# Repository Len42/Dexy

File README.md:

# Dexy

_DX7-inspired FM synthesis with a Raspberry Pi Pico_

Dexy is a digital FM voice in a 10 HP module. Part of my [homebrew Eurorack synthesizer](https://lenp.net/synth/).

[See here](https://lenp.net/synth/dexy/) for more info.

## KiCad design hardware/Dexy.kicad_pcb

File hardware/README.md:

# Dexy Hardware

Dexy is a digital FM voice module based on an [RP2040 microcontroller](https://www.raspberrypi.com/documentation/microcontrollers/rp2040.html).

[See here](https://lenp.net/synth/dexy/hardware.html) for more info.

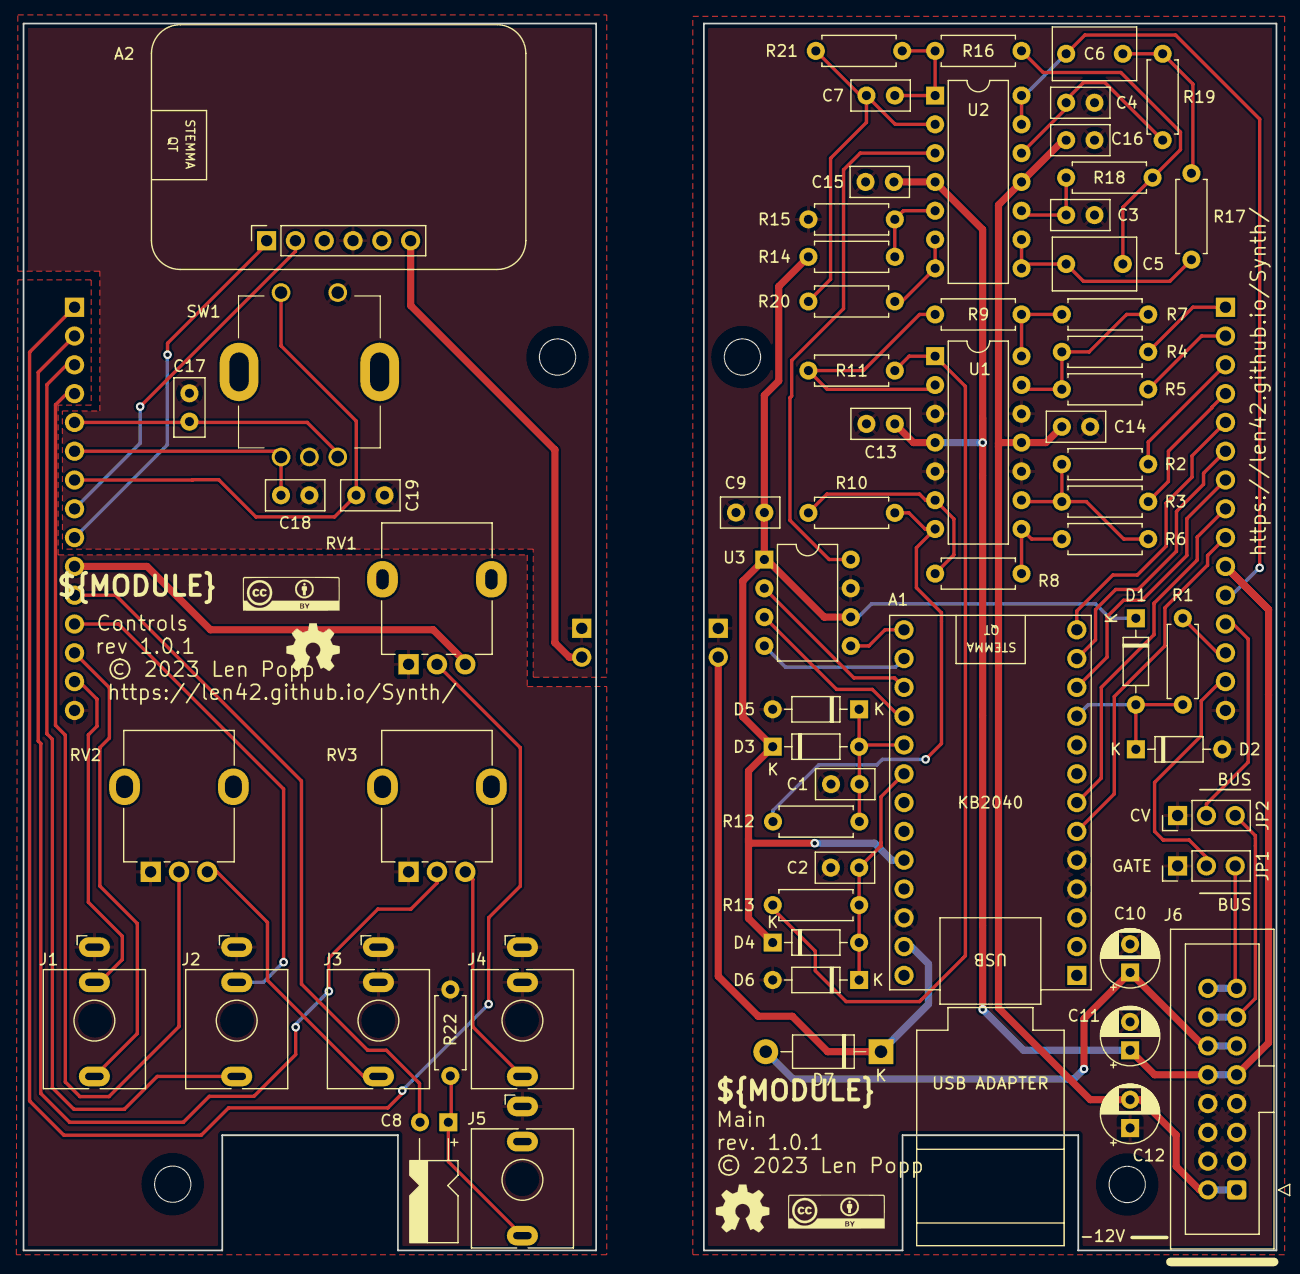
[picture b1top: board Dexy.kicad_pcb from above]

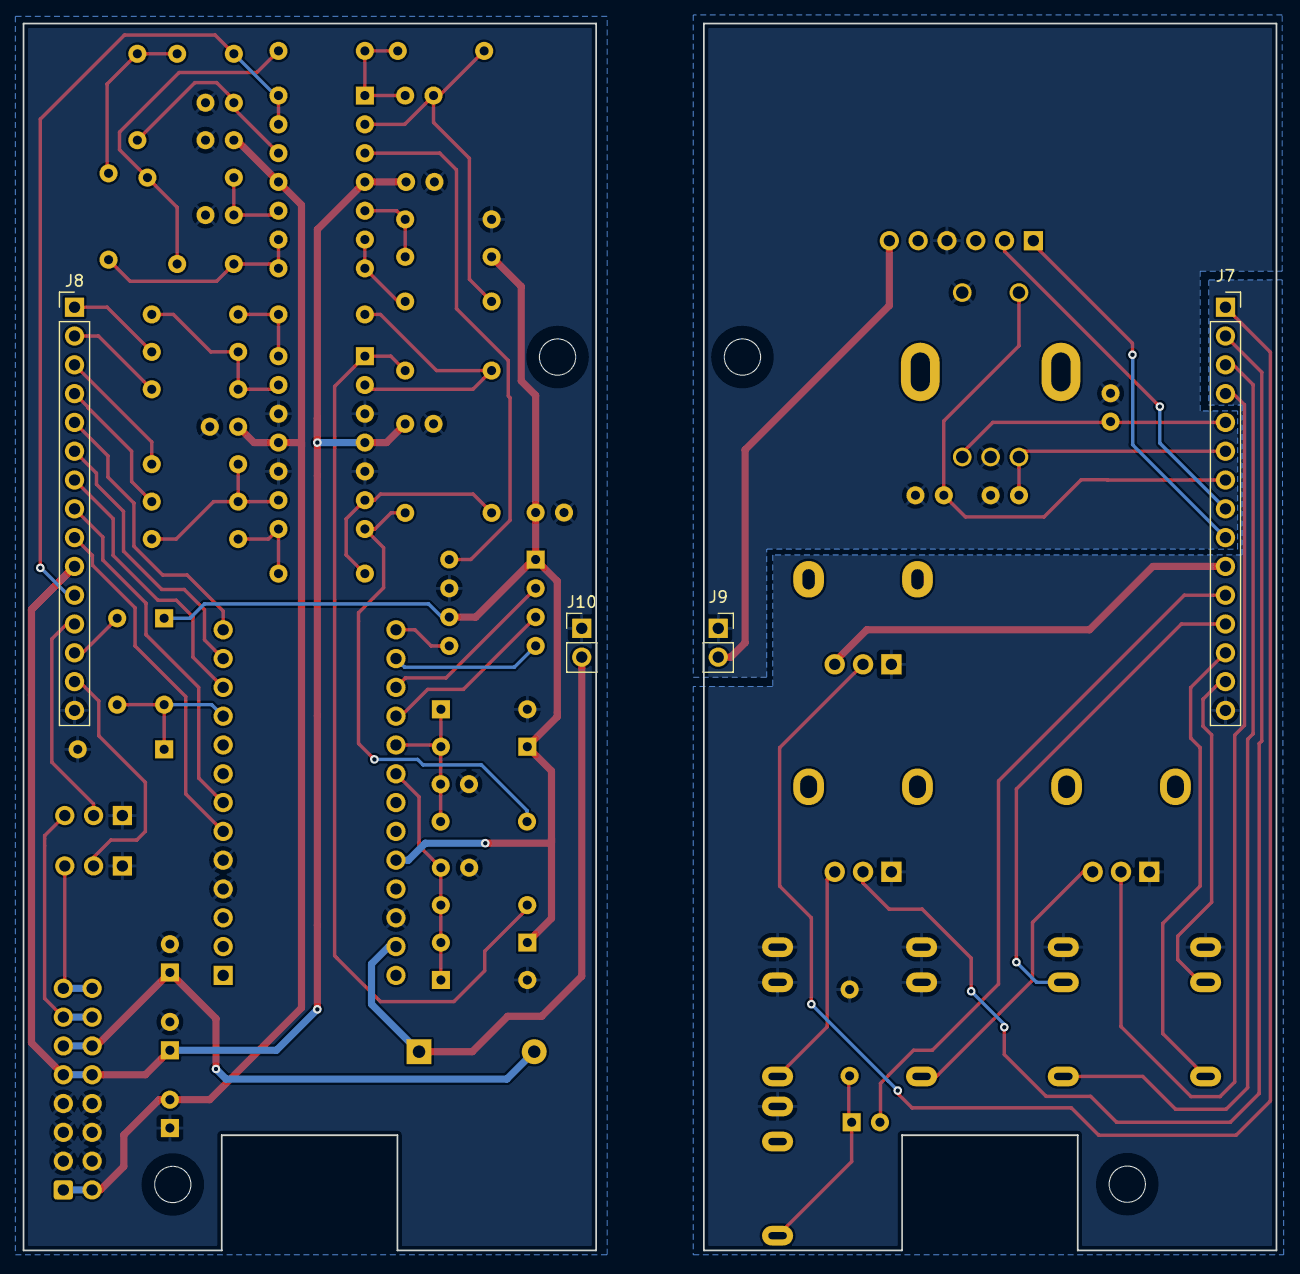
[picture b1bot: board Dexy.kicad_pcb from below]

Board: 2 copper layers, 110.5 x 108.2 mm, 78 parts (4 on the bottom side), 49 nets.

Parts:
A1: KB2040
A2: OLED_128x32; OLED_128x32_0.91in_NoHoles
A4: USB C Adapter 90deg; USB-C-Adapter-90-Outline
C1, C2, C3, C4: 150P; C_Disc_D5.0mm_W2.5mm_P2.50mm
C5, C6: 330P; C_Rect_L7.2mm_W4.5mm_P5.00mm
C7: 5P6; C_Disc_D5.0mm_W2.5mm_P2.50mm
C8: 2U2; CP_Radial_L7.0mm_D4.0mm_P2.50mm_Horiz
C9, C13, C14, C15, C16, C17, C18, C19: 100N; C_Disc_D5.0mm_W2.5mm_P2.50mm
C10, C11, C12: 10U; CP_Radial_D5.0mm_P2.50mm
D1, D2, D3, D4, D5, D6: 1N5711; D_DO-35_SOD27_P7.62mm_Horizontal
D7: 1N4001; D_DO-41_SOD81_P10.16mm_Horizontal
G1, G2: LOGO; Logo_CC_BY
G3, G4: LOGO; Logo_OSHW
H1, H2, H3, H4: MountingHole_M3; MountingHole_PCB_3.2mm_M3
J1, J2, J3, J4, J5: WQP-PJ398; Jack_3.5mm_QingPu_WQP-PJ398SM_Vertical
J6: Conn_Eurorack_16; IDC-Header-Eurorack-16-TH
J7: Controls_Left; PinSocket_1x15_P2.54mm_Vertical
J8: Main_Right; PinHeader_1x15_P2.54mm_Vertical
J9: Controls_Right; PinSocket_1x02_P2.54mm_Vertical
J10: Main_Left; PinHeader_1x02_P2.54mm_Vertical
JP1, JP2: Jumper_Pins_3_Bridged12; PinHeader_1x03_P2.54mm_Vertical
R1, R2, R6, R7, R8, R9, R12, R13: 100K; R_Axial_DIN0207_L6.3mm_D2.5mm_P7.62mm_Horizontal
R3: 499K; R_Axial_DIN0207_L6.3mm_D2.5mm_P7.62mm_Horizontal
R4: 120K; R_Axial_DIN0207_L6.3mm_D2.5mm_P7.62mm_Horizontal
R5: 82K; R_Axial_DIN0207_L6.3mm_D2.5mm_P7.62mm_Horizontal
R10, R11, R15: 33K; R_Axial_DIN0207_L6.3mm_D2.5mm_P7.62mm_Horizontal
R14, R20: 51K; R_Axial_DIN0207_L6.3mm_D2.5mm_P7.62mm_Horizontal
R16, R17, R18, R19: 47K; R_Axial_DIN0207_L6.3mm_D2.5mm_P7.62mm_Horizontal
R21: 200K; R_Axial_DIN0207_L6.3mm_D2.5mm_P7.62mm_Horizontal
R22: 1M; R_Axial_DIN0207_L6.3mm_D2.5mm_P7.62mm_Horizontal
RV1: 100K; Potentiometer_Alpha_RD901F-40-00D_Single_Vertical
RV2, RV3: 100K; Potentiometer_SongHuei_Single_Vertical
SW1: PEC11R-4x20x-S00xx; Encoder_Bourns_PEC11R_Switch
U1, U2: TL074; DIP-14_W7.62mm
U3: MCP4821; DIP-8_W7.62mm

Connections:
+3V3: A1.22 (3V3), C9.2, D1.1 (K), D3.1 (K), D4.1 (K), R14.1, U3.1 (V+), U3.6 (~SHDN)
+5V: A1.25 (V-RAW), A2.6 (VIN), D7.1 (K), J9.2, J10.2
+12V: C11.1, C13.1, C15.1, J6.9 (+12V), J6.10, J7.10, J8.10, RV1.3, U1.4 (V+), U2.4 (V+)
-12V: C12.2, C14.2, C16.2, J6.1 (-12V), J6.2, U1.11 (V-), U2.11 (V-)
/1V30: R20.1, U2.6 (-), U2.7
/10Vp-p: C7.2, R16.1, R21.2, U2.1
ADC-PITCH: A1.18 (A0(GPIO26/SCK1/CTS1/SDA1/PWM5A)), C1.1, D3.2 (A), D5.1 (K), R12.2
ADC-TIMBRE: A1.19 (A1(GPIO27/TX1/RTS1/SCL1/PWM5B)), C2.1, D4.2 (A), D6.1 (K), R13.2
AUDIO-OUT: C6.2, C8.2, J7.11, J8.11, U2.13 (-), U2.14
BUS-CV: J2.TN, J7.12, J8.12, JP2.2 (C)
BUS-GATE: J1.TN, J7.14, J8.14, JP1.2 (C)
DAC-OUT: U2.3 (+), U3.8 (Vout)
ENC-A: A1.12 (D8(GPIO8/RX1/TX1/SDA0/PWM4A)), C18.1, J7.6, J8.6, SW1.A
ENC-B: A1.13 (D9(GPIO9/CSN1/RX1/SCL0/PWM4B)), C17.1, J7.5, J8.5, SW1.B
ENC-SW: A1.11 (D7(GPIO7/TX0/RTS1/SCL1/PWM3B)), C19.1, J7.7, J8.7, SW1.S1
GATE: A1.10 (D6(GPIO6/SCK0/CTS1/SDA1/PWM3A)), D1.2 (A), D2.1 (K), R1.2
GND: A1.4 (GND), A1.5 (GND), A1.24 (GND), A2.4 (GND), C1.2, C2.2, C3.2, C4.2, C9.1, C10.2, C11.2, C12.1, C13.2, C14.1, C15.2, C16.1, C17.2, C18.2, C19.2, D2.2 (A), D5.2 (A), D6.2 (A), J1.S, J2.S, J3.S, J3.TN, J4.S, J4.TN, J5.S, J6.3 (GND), J6.4, J6.5 (GND), J6.6, J6.7 (GND), J6.8, J7.15, J8.15, J9.1, J10.1, JP1.1 (A), JP2.1 (A), R15.2, R22.2, RV1.1, RV2.1, RV3.1, SW1.C, SW1.S2, U1.3 (+), U1.5 (+), U1.10 (+), U1.12 (+), U3.7 (V-)
I2C-SCL: A1.7 (D3(GPIO3/TX0/RTS0/SCL1/PWM1B)), A2.2 (SCL), J7.8, J8.8
I2C-SDA: A1.6 (D2(GPIO2/SCK0/CTS0/SDA1/PWM1A)), A2.1 (SDA), J7.9, J8.9
IN-CV-PITCH: J2.T, J7.3, J8.3, R2.1
IN-CV-PITCH-MOD: J7.4, J8.4, R3.1, RV2.2
IN-CV-TIMBRE: J7.1, J8.1, R4.1, RV1.2
IN-CV-TIMBRE-MOD: J7.2, J8.2, R5.1, RV3.2
IN-GATE: J1.T, J7.13, J8.13, R1.1
unnamed: C5.1, R16.2, R18.1
unnamed: C6.1, R17.2, R19.1
unnamed: C8.1, J5.T, R22.1
unnamed: C10.1, D7.2 (A), J6.11 (+5V), J6.12
unnamed: J3.T, RV2.3
unnamed: J4.T, RV3.3
unnamed: J6.13 (CV), J6.14, JP2.3 (B)
unnamed: J6.15 (GATE), J6.16, JP1.3 (B)
unnamed: R6.2, R8.1, U1.8
unnamed: R7.2, R9.1, U1.14
unnamed: R10.2, R12.1, U1.7
unnamed: R11.2, R13.1, U1.1
unnamed: R9.2, R11.1, U1.2 (-)
unnamed: R8.2, R10.1, U1.6 (-)
unnamed: R2.2, R3.2, R6.1, U1.9 (-)
unnamed: R4.2, R5.2, R7.1, U1.13 (-)
unnamed: C7.1, R20.2, R21.1, U2.2 (-)
unnamed: R14.2, R15.1, U2.5 (+)
unnamed: C3.1, R18.2, U2.10 (+)
unnamed: C5.2, R17.1, U2.8, U2.9 (-)
unnamed: C4.1, R19.2, U2.12 (+)
SPI-SCK: A1.17 (SCK(GPIO18/SCK0/CTS0/SDA1/PWM1A)), U3.3 (SCK)
SPI-SDI: A1.15 (MOSI(GPIO19/TX0/RTS0/SCL1/PWM1B)), U3.4 (SDI)
~LDAC: A1.14 (D10(GPIO10/SCK1/CTS1/SDA1/PWM5A)), U3.5 (~LDAC)
~SPI-CS: A1.16 (MISO(GPIO20/RX0/TX1/SDA0/PWM2A)), U3.2 (~CS)

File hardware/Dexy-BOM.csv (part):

Ref,Qty,Value,Value2,Note,Description,Datasheet,Manufacturer,ManuPartNum,Distributor1,DistributorPartNum1,DistributorPartLink1,Distributor2,DistributorPartNum2,DistributorPartLink2,Distributor3,DistributorPartNum3,DistributorPartLink3
"A1","1","KB2040","","","Adafruit Feather RP2040 microcontroller dev board","https://learn.adafruit.com/adafruit-feather-rp2040-pico","Adafruit","4884","Adafruit","4884","https://www.adafruit.com/product/4884","","","","","",""
"A2","1","OLED_128x32","","","OLED display module 128x32 pixels I2C with header, STEMMA-QT connectors","https://learn.adafruit.com/monochrome-oled-breakouts","Adafruit","4440","Adafruit","4440","https://www.adafruit.com/product/4440","","","","","",""
"A3","1","Cable_Eurorack_16","","Length as required","Eurorack 16-16 pin power & bus cable","","","","Thonk","","https://www.thonk.co.uk/shop/eurorack-power-cables/","SynthCube","","https://synthcube.com/cart/eurorack-ribbon-power-cables","Modular Addict","","https://modularaddict.com/parts/eurorack-power-cables-1"
"A4","1","USB C Adapter 90deg","","","Miscellaneous","","AFUNTA","","Amazon","","https://www.amazon.ca/Degree-Adapter-AFUNTA-Downward-Extensi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","","","","","",""
"C1 C2 C3 C4","4","150P","C0G/NP0","","Capacitor - Ceramic","https://www.mouser.ca/datasheet/2/427/kseries-1763315.pdf","Vishay/BC","K151J15C0GF5TL2","Mouser","594-K151J15C0GF5TL2","https://www.mouser.ca/ProductDetail/?qs=B4Lc6Tv24ta3ZLBKnPGb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","","","","","",""
"C5 C6","2","330P","","","Capacitor - Ceramic","https://www.mouser.ca/datasheet/2/212/1/KEM_F3036_PFR-1102852.pdf","KEMET","PFR5331J63J11L4BULK","Mouser","80-PFR5331J63J11L4","https://www.mouser.ca/ProductDetail/KEMET/PFR5331J63J11L4BUL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","","","","","",""
"C7","1","5P6","C0G/NP0","","Capacitor - Ceramic","https://www.mouser.ca/datasheet/2/212/KEM_C1049_GOLDMAX_C0G-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","KEMET","C315C569D1G5TA","Mouser","80-C315C569D1G","https://www.mouser.ca/ProductDetail/KEMET/C315C569D1G5TA?qs=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","","","","","",""
"C8","1","2U2","","","Capacitor - Electrolytic","https://www.mouser.ca/datasheet/2/315/ABA0000C1050-947578.pdf","Panasonic","ECE-A1HKA2R2I","Mouser","667-ECE-A1HKA2R2I","https://www.mouser.ca/ProductDetail/Panasonic/ECE-A1HKA2R2I?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","","","","","",""
"C9 C13 C14 C15 C16 C17 C18 C19","8","100N","","IC decoupling","Capacitor - Ceramic - IC decoupling","https://product.tdk.com/system/files/dam/doc/product/capacit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","TDK","FG18X7R1H104KNT06","Mouser","810-FG18X7R1H104KNT6","https://www.mouser.ca/ProductDetail/810-FG18X7R1H104KNT6","","","","","",""
"C10 C11 C12","3","10U","35 VDC","12 V decoupling","Capacitor - Electrolytic - 12 V decoupling","https://www.mouser.ca/datasheet/2/315/ABA0000C1059-947582.pdf","Panasonic","ECE-A1VKS100I","Mouser","667-ECE-A1VKS100I","https://www.mouser.ca/ProductDetail/667-ECE-A1VKS100I","Thonk","Group_Eurorack_DIY_Essential","https://www.thonk.co.uk/shop/eurorack-diy-essentials/","","",""
"D1 D2 D3 D4 D5 D6","6","1N5711","","","Schottky signal diode","https://www.mouser.ca/datasheet/2/389/cd00000759-1795802.pdf","STMicroelectronics","1N5711","Mouser","511-1N5711","https://www.mouser.ca/ProductDetail/STMicroelectronics/1N571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","","","","","",""
"D7","1","1N4001","","","50V 1A General Purpose Rectifier Diode, DO-41","https://www.mouser.ca/datasheet/2/308/1N4001_D-1801424.pdf","onsemi","1N4001G","Mouser","863-1N4001G","https://www.mouser.ca/ProductDetail/onsemi/1N4001G?qs=y2kkmE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","","","","","",""
"H5 H7 H8 H10","4","HW_Screw_M3x0.50x6","","","Machine screw, M3x0.50x6","","","","","","","","","","","",""
"H6 H9","2","HW_Standoff_F-F_11mm_M3x0.50","","","Standoff, 11mm, female-female, M3x0.50","https://www.thonk.co.uk/wp-content/uploads/2018/05/standoff-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","Ettinger","05.03.111","Thonk","Mech_11mm_Standoff_(x10)","https://www.thonk.co.uk/shop/standoffs/","Mouser","710-970110321","https://www.mouser.ca/ProductDetail/Wurth-Elektronik/9701103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","Mouser","144-MTS-11","https://www.mouser.ca/ProductDetail/144-MTS-11"
"H11 H12","2","Jumper_2","","","Jumper connector, 2-pin socket","https://www.mouser.ca/datasheet/2/209/KC-301174-1171759.pdf","","","Mouser","151-8013-E","https://www.mouser.ca/ProductDetail/Kobiconn/151-8013-E?qs=R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","Adafruit","3525","https://www.adafruit.com/product/3525","","",""
"J1 J2 J3 J4 J5","5","WQP-PJ398","","","Audio Jack, 2 Poles (Mono / TS), Switched T Pole (Normalling), QingPu / Thonkiconn","http://www.qingpu-electronics.com/en/products/WQP-PJ398SM-362.html","QingPu / Thonk","PJ398SM / WQP518MA","Thonk","PJ398SM","https://www.thonk.co.uk/shop/thonkiconn/","SynthCube","WQP518MA","https://synthcube.com/cart/3-5mm-euro-jacks","Adafruit","4031","https://www.adafruit.com/product/4031"
"J6","1","Conn_Eurorack_16","","","Eurorack 16-pin board power/CV/gate bus connector","https://www.mouser.ca/datasheet/2/445/61201621621-1717735.pdf","Wurth Elektronik","61201621621","Mouser","710-61201621621","https://www.mouser.ca/ProductDetail/Wurth-Elektronik/6120162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","","","","","",""
"J7","1","Controls_Left","","","Generic connector, single row, 01x15, script generated (kicad-library-utils/schlib/autogen/connector/)","","","","Adafruit","598","https://www.adafruit.com/product/598","Mouser","710-61303211821","https://www.mouser.ca/ProductDetail/Wurth-Elektronik/6130321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","","",""
"J8","1","Main_Right","","","Generic connector, single row, 01x15, script generated (kicad-library-utils/schlib/autogen/connector/)","","","","Adafruit","392","https://www.adafruit.com/product/392","Mouser","649-1012937893601BLF","https://www.mouser.ca/ProductDetail/649-1012937893601BLF","","",""
"J9","1","Controls_Right","","","Generic connector, single row, 01x02, script generated (kicad-library-utils/schlib/autogen/connector/)","","","","Adafruit","598","https://www.adafruit.com/product/598","Mouser","710-61303211821","https://www.mouser.ca/ProductDetail/Wurth-Elektronik/6130321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","","",""
"J10","1","Main_Left","","","Generic connector, single row, 01x02, script generated (kicad-library-utils/schlib/autogen/connector/)","","","","Adafruit","392","https://www.adafruit.com/product/392","Mouser","649-1012937893601BLF","https://www.mouser.ca/ProductDetail/649-1012937893601BLF","","",""
"J11","1","Conn_01x06","","OLED module needs a header connector with 8mm pins","Generic connector, single row, 01x06, script generated (kicad-library-utils/schlib/autogen/connector/)","https://www.amphenol-icc.com/media/wysiwyg/files/documentati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","Amphenol FCI","10129378-936003BLF","Mouser","649-1012937893603BLF","https://www.mouser.ca/ProductDetail/Amphenol-FCI/10129378-93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","","","","","",""
"JP1 JP2","2","Jumper_Pins_3_Bridged12","","","Jumper pins, 3-pole, pins 1+2 closed/bridged","","","","Adafruit","392","https://www.adafruit.com/product/392","Mouser","649-1012937893601BLF","https://www.mouser.ca/ProductDetail/649-1012937893601BLF","","",""
"R1 R7 R9 R12 R13","5","100K","1%, 1/6 W","","Resistor","https://www.mouser.ca/datasheet/2/447/Yageo_LR_MFR_1-1714151.pdf","YAGEO","MFR-12FTF52-100K","Mouser"," 603-MFR-12FTF52-100K","https://www.mouser.ca/c/?m=YAGEO&power+rating=166+mW+(1%2f6+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","","","","","",""
"R2 R6 R8","3","100K","0.1%","","Resistor","https://www.mouser.ca/datasheet/2/427/cmfmil-1762972.pdf","Vishay / Dale","RN55C1003BRE6","Mouser","71-RN55C-B-100K/R","https://www.mouser.ca/ProductDetail/Vishay-Dale/RN55C1003BRE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","","","","","",""
"R3","1","499K","1%","","Resistor","https://www.mouser.ca/datasheet/2/447/Yageo_LR_MFR_1-1714151.pdf","YAGEO","MFR-25FBF52-499K","Mouser","603-MFR-25FBF52-499K","https://www.mouser.ca/ProductDetail/?qs=oAGoVhmvjhzlnFbAvm5I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","","","","","",""
"R4","1","120K","1%, 1/6 W","","Resistor","https://www.mouser.ca/datasheet/2/447/Yageo_LR_MFR_1-1714151.pdf","YAGEO","MFR-12FTF52-120K","Mouser","603-MFR-12FTF52-120K","https://www.mouser.ca/ProductDetail/YAGEO/MFR-12FTF52-120K?q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","","","","","",""
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
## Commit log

2023-07-23 add a note to hardware/README.md
2023-07-25 firmware: include binary data files - wip
2023-07-26 firmware: include binary patch file - wip
2023-07-26 firmware: include binary patch file
2023-07-26 Include binary file for default patches in firmware (#1)
    firmware: include binary patch file
2023-07-27 patch editing
2023-07-27 fix envelope clicks - wip
2023-07-27 fix envelope clicks
2023-07-27 Firmware: Envelope tweaks (#2)
    fix envelope clicks
2023-10-02 firmware: Improvements to feedback amount and output averaging
    (cherry picked from commit a8f856a2cd19b8b7c53dc3b6828964d3d50aac1d)
2023-10-04 DexyPatch: updated algorithm icons
    (cherry picked from commit 96be5512da9439649c4f0df8c18e633811be0a7a)
2023-10-05 DexyPatch: better envelope outlines
2023-10-21 firmware: Display::drawText has fewer overloads and uses string_view instead of char*
2023-10-21 firmware - update the default patch bank
2023-11-04 update "Software Used" in readmes
2023-11-12 DexyPatch: ErrorLog enhancements
2023-11-12 DexyPatch: stub implementation of IMessageBoxService
2023-11-12 DexyPatch: rename MessageBoxService -> DialogService
2023-11-12 DexyPatch: #if out some stuff in DialogService
2023-11-12 DexyPatch: update Avalonia to version 11 - well, it compiles, mostly...
2023-11-13 DexyPatch: fix incorrect command handler method names (which somehow worked before)
2023-11-13 DexyPatch: disable auto-scrolling of Dexy serial output window becuase it's fubar in Avalonia 11
2023-11-13 DexyPatch: update MessageBox.Avalonia package to the latest version
2023-11-13 DexyPatch: re-do Open File dialogs - wip
2023-11-13 DexyPatch: re-do Open File dialogs - done
2023-11-13 DexyPatch: update some more packages
2023-11-13 DexyPatch: cleanup after previous changes
2023-11-13 DexyPatch: fix serial text auto-scrolling after updating to Avalonia 11
2023-11-13 Changes for Avalonia UI version 11 and other package updates (#4)
2023-11-22 DexyPatch: minor initialization cleanup
2023-12-31 Firmware: Simplify lookup table declarations
2023-12-31 Firmware: DataTable: - Make the constructor consteval because it's only supposed to run at compile time - Clean up operator[]() const
2023-12-31 Firmware: keyboard scaling - just some comments
2023-12-31 Firmware: README update
2023-12-31 Firmware: fix a comment
2024-01-01 DexyPatch: Support deserialization of old data formats
2024-01-01 Firmware, DexyPatch: Add a field to the serialized operator settings
2024-01-01 Firmware, DexyPatch: Add more envelope settings to the serialized operator settings
2024-01-01 firmware: clean up some loops - wip
2024-01-01 firmware: clean up some loops
2024-01-02 firmware: make-binary-inc-file.py: better exception handling
2024-01-02 firmware: clean up doc comments
2024-02-15 Revert "firmware - update the default patch bank"
2024-03-24 Documentation moved from READMEs to main web site
2024-04-14 Documentation moved from READMEs to main web site
    (cherry picked from commit 63189a09a256232b0417388647cdf54faaa92e7e)
2024-04-14 add a modified patchbank
2024-04-14 PatchDump: started
2024-04-14 PatchDump: remove auto-generated file version.h
2024-04-15 firmware: change definitions of Patch classes
2024-04-15 PatchDump: wip
2024-04-16 PatchDump: C++22.5 required
2024-04-17 PatchDump: back to C++20
2024-04-17 PatchDump: Templates Gone Wild!
2024-04-18 firmware: Display version number during build
2024-04-18 PatchDump: small change to output formatting
2024-04-18 PatchDump: V2 patch files - wip
2024-04-18 firmware: Change format of V2 patch data
2024-04-18 PatchDump: V2 patch files
2024-04-18 PatchDump: fix a couple of error messages
2024-04-18 PatchDump: note names
2024-04-18 DexyPatch: Fix a glitch with the frequency sliders
2024-04-18 PatchDump: clean up note naming
2024-04-19 firmware: scaling - wip
2024-04-19 PatchDump: operator parameters printed in correct display order
2024-04-19 modify default patch file - sine, saw
2024-04-20 update default patchbank
2024-04-21 DexyPatch: Change the app icon
2024-07-01 default patchbank: add epiano patch
2024-07-05 PatchDump needs LICENSE and README files
2024-07-09 simplify TaskList (slightly)
2024-07-10 firmware: much better simplification of makeTaskList()
2024-07-10 firmware: makeTaskList(): eliminate CTAD
2024-07-23 firmware: Simplify TaskList declaration
2024-08-08 hardware: PCB layout alignment changed to match template
2024-11-22 new patch - wip
2025-09-04 Add a comment in CMakeLists.txt. Boring.

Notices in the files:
hardware/Dexy.kicad_pcb:
Copyright © 2023 Len Popp CC BY
